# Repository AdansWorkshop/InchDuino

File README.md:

# InchDuino
One of many Arduino clones, but this one is 1 square inch!

An ATMega328P microcontroller and as much easily accessible I/O as possible crammed into 1 square inch. Requires some sort of USB to UART cable. UART pins are connected to programming UART pins. All UART/SPI/I²C pins are data pins by default and need to be configured. VCC = 5V. AREF is not connected to anything and needs to either be connected to a stable reference voltage or to VCC directly or through a smoothing capacitor. I have not ordered any parts or the boards yet but I do plan to.

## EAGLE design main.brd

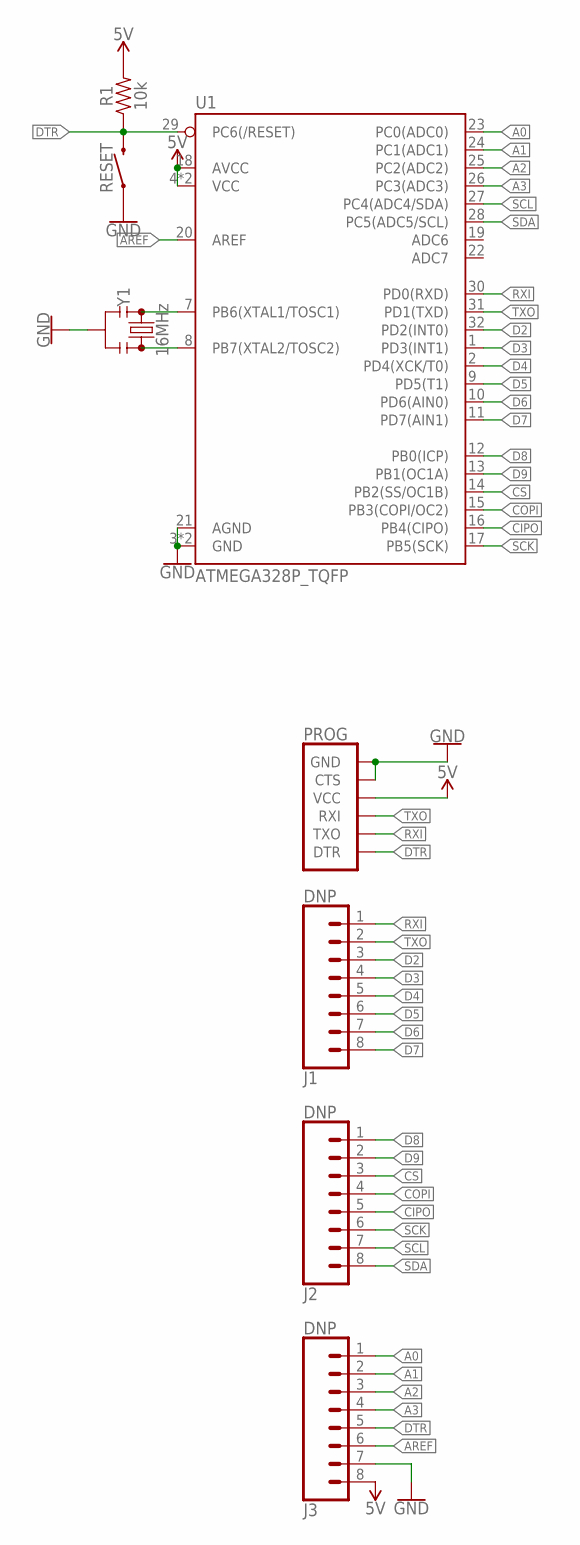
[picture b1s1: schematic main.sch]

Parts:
J1, J2, J3: DNP; 1X08
PROG: 6_PIN_SERIAL_TARGETSILK; 6_PIN_SERIAL_TARGET_SIDE_W_SILK
R1: 10k; 0402
RESET: MOMENTARY-SWITCH-SPST-SMD-6.0X3.5MM; TACTILE_SWITCH_SMD_6.0X3.5MM
U1: ATMEGA328P_TQFP; TQFP32-08
Y1: 16MHz; RESONATOR-SMD-3.2X1.3

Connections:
5V: J3.8, PROG.4 (VCC), R1.2, U1.4 (VCC), U1.6 (VCC), U1.18 (AVCC)
A0: J3.1, U1.23 (PC0(ADC0))
A1: J3.2, U1.24 (PC1(ADC1))
A2: J3.3, U1.25 (PC2(ADC2))
A3: J3.4, U1.26 (PC3(ADC3))
AREF: J3.6, U1.20 (AREF)
CIPO: J2.5, U1.16 (PB4(CIPO))
COPI: J2.4, U1.15 (PB3(COPI/OC2))
CS: J2.3, U1.14 (PB2(SS/OC1B))
D2: J1.3, U1.32 (PD2(INT0))
D3: J1.4, U1.1 (PD3(INT1))
D4: J1.5, U1.2 (PD4(XCK/T0))
D5: J1.6, U1.9 (PD5(T1))
D6: J1.7, U1.10 (PD6(AIN0))
D7: J1.8, U1.11 (PD7(AIN1))
D8: J2.1, U1.12 (PB0(ICP))
D9: J2.2, U1.13 (PB1(OC1A))
DTR: J3.5, PROG.1 (DTR), R1.1, RESET.2, U1.29 (PC6(/RESET))
GND: J3.7, PROG.5 (CTS), PROG.6 (GND), RESET.1, U1.3 (GND), U1.5 (GND), U1.21 (AGND), Y1.2
unnamed: U1.8 (PB7(XTAL2/TOSC2)), Y1.3
unnamed: U1.7 (PB6(XTAL1/TOSC1)), Y1.1
RXI: J1.1, PROG.2 (TXO), U1.30 (PD0(RXD))
SCK: J2.6, U1.17 (PB5(SCK))
SCL: J2.7, U1.27 (PC4(ADC4/SDA))
SDA: J2.8, U1.28 (PC5(ADC5/SCL))
TXO: J1.2, PROG.3 (RXI), U1.31 (PD1(TXD))

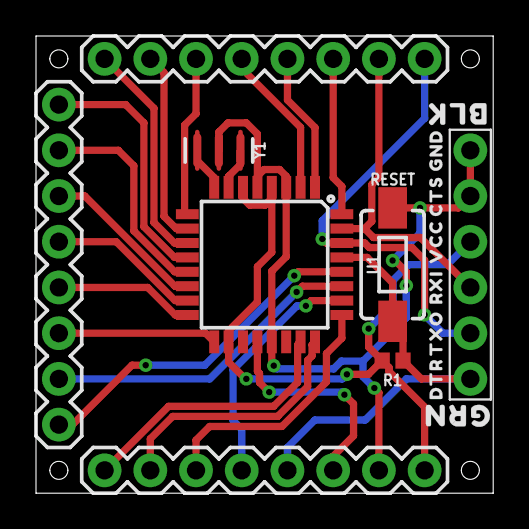
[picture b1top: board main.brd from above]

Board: 2 copper layers, 25.4 x 25.4 mm, 8 parts (0 on the bottom side), 26 nets.

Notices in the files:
parts and their libraries:
SparkFun-IC-Microcontroller: Licensing: Creative Commons ShareAlike 4.0 International - https://creativecommons.org/licenses/by-sa/4.0
